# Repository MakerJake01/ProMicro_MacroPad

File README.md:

# ProMicro_MacroPad

**Overview** <br>
This project is for anyone who wants to make an 8 key MacroPad. The parts will most likely cost more than buying one. It can be used for keybinds in many programs. 
It's perfect for switching between scenes in OBS or a mute/unmute button in Discord. Some of the code is probably not the most efficient as I am a beginner. I am looking into making it work with QMK. 

<blockquote class="imgur-embed-pub" lang="en" data-id="a/6hcVxPT"  ><a href="//imgur.com/a/6hcVxPT">MacroPad pics</a></blockquote>

**The programing:** <br>
The code was all programmed in C++ using the Arduino IDE. It can be programmed with F keys (i.e. F13, F14, ...).
It uses the [keyboard.h](https://www.arduino.cc/reference/en/language/functions/usb/keyboard/) library. I have tried to make it as easy to reprogram as possible. 
It may be possible to program the MacroPad more efficiently. 

**The soldering:** <br>
There is a lot of SMD soldering. The smallest parts are 1206 resistors and capacitors. Some of the pads for the LEDs on the back do get very close. It will be an intermediate to advanced soldering project. (I have been soldering for a while so, SMD soldering is easy for me.) [SMD Soldering Guide](https://www.youtube.com/watch?v=VxMV6wGS3NY&t=544s)

**The PCB:** <br>
Use the Gerber files to make the PCBs. It's a two-layer PCB and a 1.6 mm board. A black solder mask will look better but will add some time and possible cost.  

**The switches** <br>
The PCB has the holes for an MX style switch. The PCB has the holes for a plate mount switch. If you have a PCB mount switch, the extra legs need to be cut off.

**Build guide** <br>
I am working on a multi-part build guide for my youtube channel.  
https://www.youtube.com/makerjake

**printed parts** <br>
I am having some trouble finding the STL files and my fusion 360 subscriptions has run out. I will try to either redesign the parts of finding the files. 

Creative Commons Attribution-NonCommercial 4.0 International License. cc-by-nc

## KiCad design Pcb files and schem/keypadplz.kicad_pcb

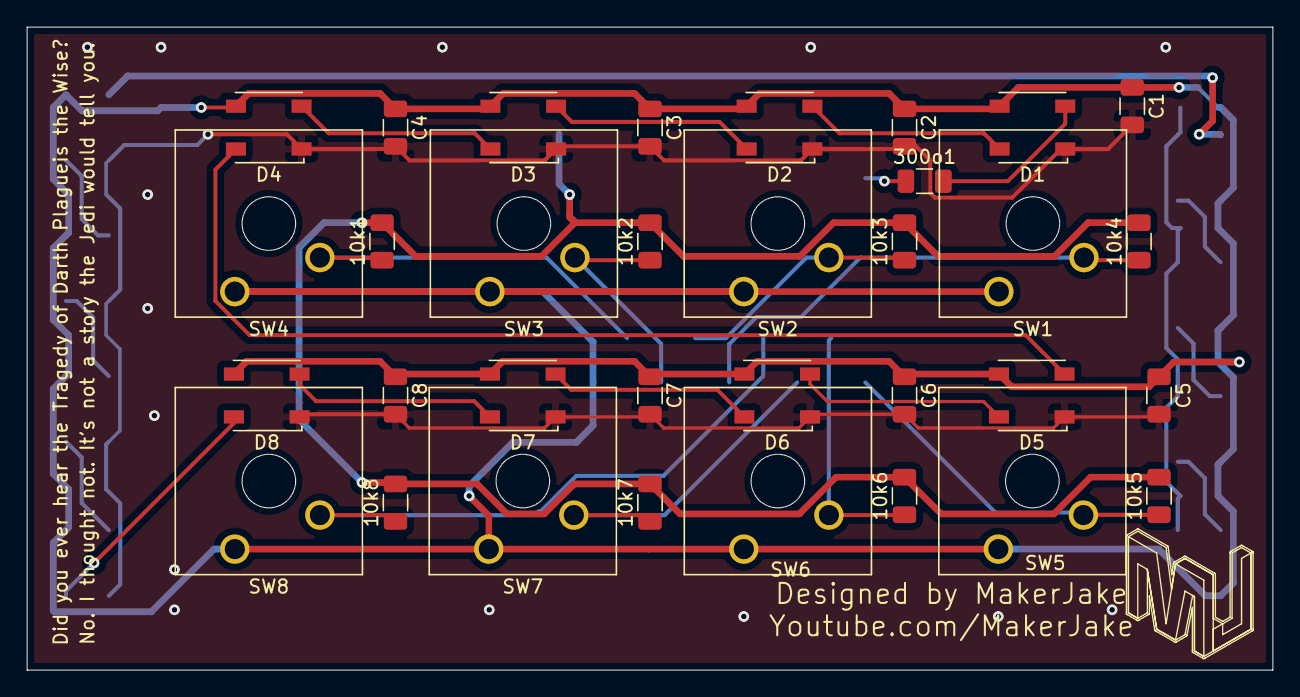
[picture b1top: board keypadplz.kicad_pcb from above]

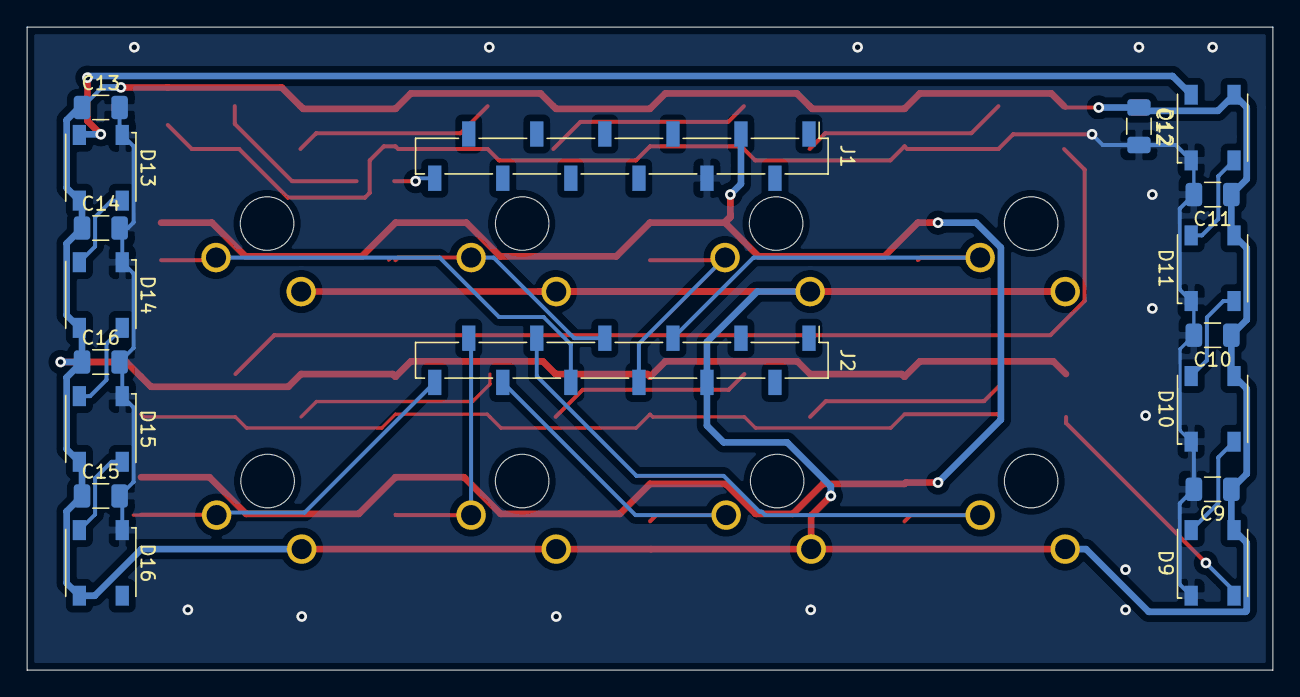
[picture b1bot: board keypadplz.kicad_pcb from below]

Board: 2 copper layers, 93.0 x 48.0 mm, 51 parts (18 on the bottom side), 28 nets.

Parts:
10k1, 10k2, 10k3, 10k4, 10k5, 10k6, 10k7, 10k8: R1; R_1206_3216Metric
300o1: R; R_1206_3216Metric
C1, C2, C3, C4, C5, C6, C7, C8, C9, C10, C11, C12, C13, C14, C15, C16: C_Small; C_1206_3216Metric
D1, D2, D3, D4, D5, D6, D7, D8, D9, D10, D11, D12, D13, D14, D15, D16: Inolux_IN-PI554FCH; LED_Inolux_IN-PI554FCH_PLCC4_5.0x5.0mm_P3.2mm
J1, J2: Conn_01x12_Male; PinSocket_1x12_P2.54mm_Vertical_SMD_Pin1Left
SW1, SW2, SW3, SW4, SW5, SW6, SW7, SW8: SW_Push; SW_Cherry_MX_1.00u_Plate

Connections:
GND: C1.2, C2.2, C3.2, C4.2, C5.2, C6.2, C7.2, C8.2, C9.2, C10.2, C11.2, C12.2, C13.2, C14.2, C15.2, C16.2, D1.1, D2.1, D3.1, D4.1, D5.1, D6.1, D7.1, D8.1, D9.1, D10.1, D11.1, D12.1, D13.1, D14.1, D15.1, D16.1, J1.4
unnamed: 10k1.1, J2.5, SW4.2
unnamed: 10k1.2, 10k2.2, 10k3.2, 10k4.2, 10k5.2, 10k6.2, 10k7.2, 10k8.2, J1.3
unnamed: 10k2.1, J2.6, SW3.2
unnamed: 10k3.1, J2.7, SW2.2
unnamed: 10k4.1, J2.8, SW1.2
unnamed: 10k5.1, J2.12, SW5.2
unnamed: 10k6.1, J2.11, SW6.2
unnamed: 10k7.1, J2.10, SW7.2
unnamed: 10k8.1, J2.9, SW8.2
unnamed: 300o1.1, J1.12
unnamed: 300o1.2, D1.2
unnamed: C1.1, C2.1, C3.1, C4.1, C5.1, C6.1, C7.1, C8.1, C9.1, C10.1, C11.1, C12.1, C13.1, C14.1, C15.1, C16.1, D1.3, D2.3, D3.3, D4.3, D5.3, D6.3, D7.3, D8.3, D9.3, D10.3, D11.3, D12.3, D13.3, D14.3, D15.3, D16.3, J2.4, SW1.1, SW2.1, SW3.1, SW4.1, SW5.1, SW6.1, SW7.1, SW8.1
unnamed: D1.4, D2.2
unnamed: D2.4, D3.2
unnamed: D3.4, D4.2
unnamed: D4.4, D5.2
unnamed: D5.4, D6.2
unnamed: D6.4, D7.2
unnamed: D7.4, D8.2
unnamed: D8.4, D9.2
unnamed: D9.4, D10.2
unnamed: D10.4, D11.2
unnamed: D11.4, D12.2
unnamed: D12.4, D13.2
unnamed: D13.4, D14.2
unnamed: D14.4, D15.2
unnamed: D15.4, D16.2

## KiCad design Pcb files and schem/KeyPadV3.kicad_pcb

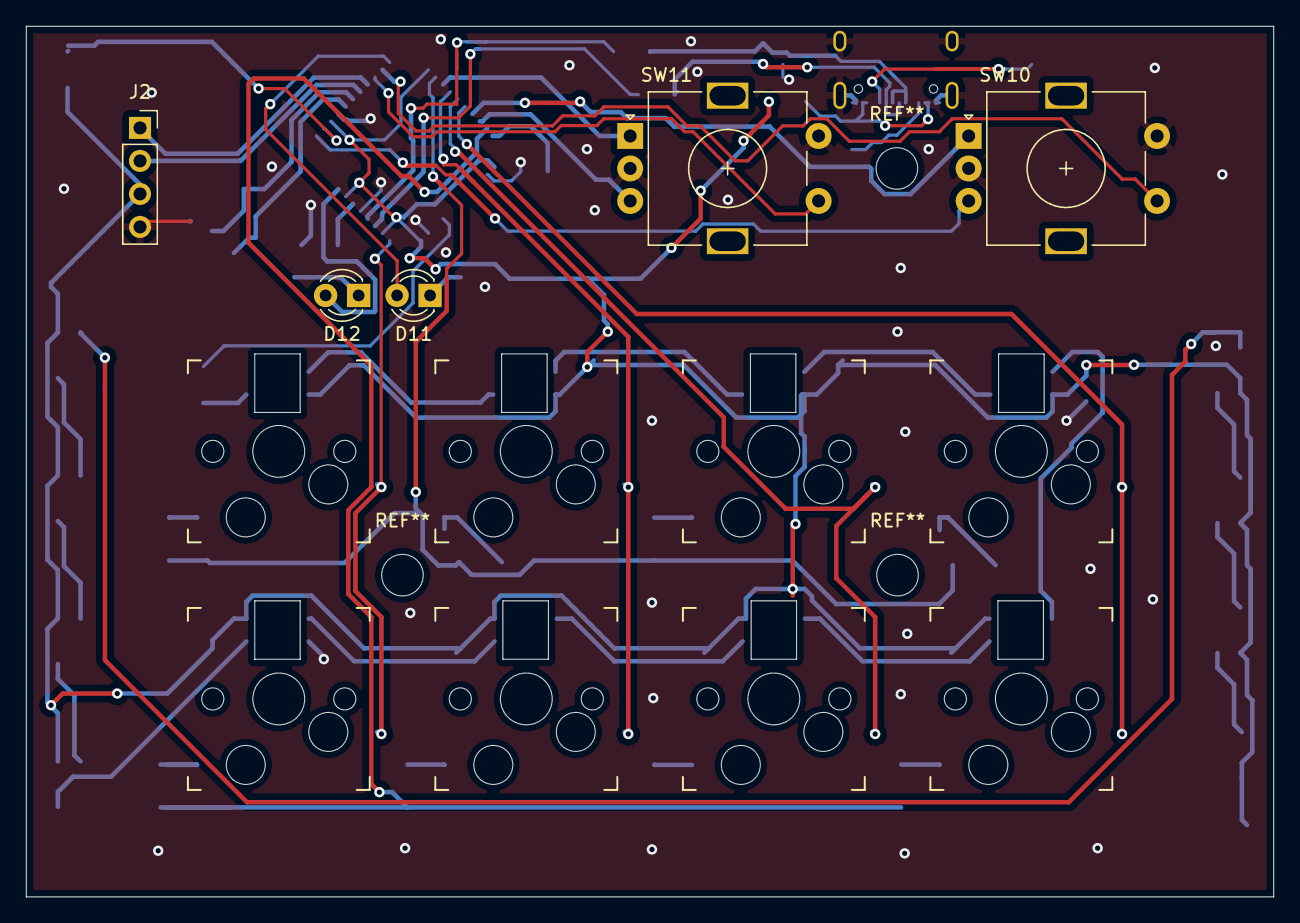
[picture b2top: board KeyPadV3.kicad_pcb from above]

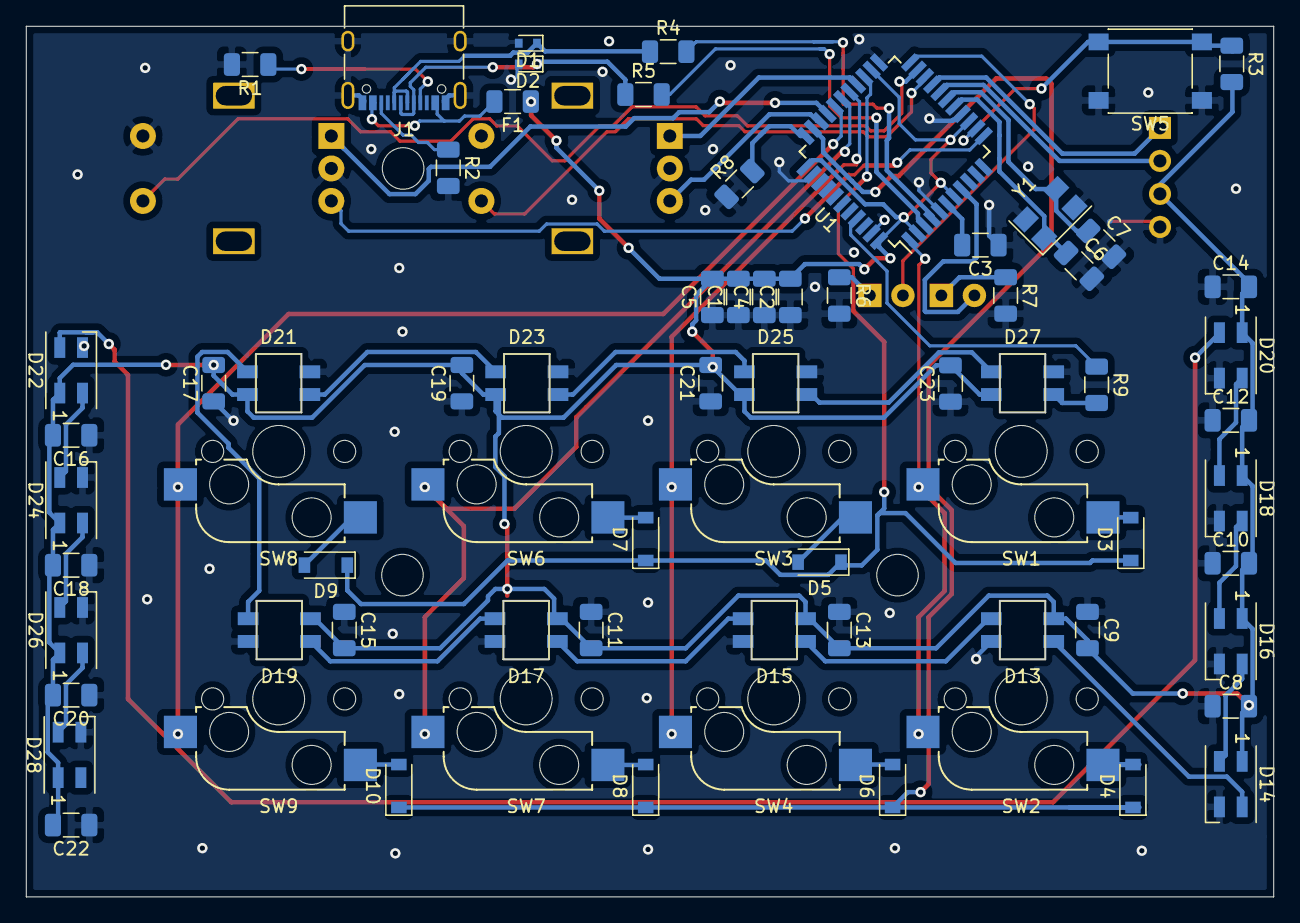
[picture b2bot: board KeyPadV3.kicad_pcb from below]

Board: 2 copper layers, 96.0 x 67.0 mm, 76 parts (63 on the bottom side), 57 nets.

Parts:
C1, C2, C4: 0.1uF; C_1206_3216Metric
C3: 1uF; C_1206_3216Metric
C5: 10uF; C_1206_3216Metric
C6, C7: 22pf; C_1206_3216Metric
C8, C9, C10, C11, C12, C13, C14, C15, C16, C17, C18, C19, C20, C21, C22, C23: .1uF; C_1206_3216Metric
D1, D2: DZ2S036X0L; D_SOD-523
D3, D4, D5, D6, D7, D8, D9, D10: D; D_SOD-123
D11, D12: LED; LED_D3.0mm
D13, D15, D17, D19, D21, D23, D25, D27: SK6812MINI; SK6812MINI_reverse
D14, D16, D18, D20, D22, D24, D26, D28: SK6812MINI; LED_SK6812MINI_PLCC4_3.5x3.5mm_P1.75mm
F1: Fuse; Fuse_1206_3216Metric
J1: USB_C_Receptacle_USB2.0; USB_C_Receptacle_XKB_U262-16XN-4BVC11
J2: Oled; PinSocket_1x04_P2.54mm_Vertical
R1, R2: 5.1k; R_1206_3216Metric
R3, R8: 10k; R_1206_3216Metric
R4, R5: 22; R_1206_3216Metric
R6, R7: 100; R_1206_3216Metric
R9: 500; R_1206_3216Metric
SW1, SW2, SW3, SW4, SW6, SW7, SW8, SW9: Switch_SW_Push; Kailh_socket_MX
SW5: SW_PUSH; SW_Push_1P1T_NO_6x6mm_H9.5mm
SW10, SW11: Rotary_Encoder_Switch; RotaryEncoder_Alps_EC11E-Switch_Vertical_H20mm
U1: ATMEGA32U4; TQFP-44_10x10mm_P0.8mm
Y1: Crystal_GND24_Small; Crystal_SMD_5032-4Pin_5.0x3.2mm

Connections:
+5V: C1.2, C2.2, C4.2, C5.2, C8.2, C9.2, C10.2, C11.2, C12.2, C13.2, C14.2, C15.2, C16.2, C17.2, C18.2, C19.2, C20.2, C21.2, C22.2, C23.2, D13.1, D14.1, D15.1, D16.1, D17.1, D18.1, D19.1, D20.1, D21.1, D22.1, D23.1, D24.1, D25.1, D26.1, D27.1, D28.1, F1.1, J2.3, R3.2, U1.2, U1.7, U1.14, U1.24, U1.34, U1.44
A1: SW10.A, U1.30
A2: SW11.A, U1.26
B1: SW10.B, U1.12
B2: SW11.B, U1.31
Col1: SW1.2, SW2.2, U1.1
Col2: SW3.2, SW4.2, U1.27
Col3: SW6.2, SW7.2, U1.28
Col4: SW8.2, SW9.2, U1.29
D+: D1.1, J1.A6, J1.B6, R4.1
D-: D2.1, J1.A7, J1.B7, R5.1
GND: C1.1, C2.1, C3.1, C4.1, C5.1, C6.2, C7.2, C8.1, C9.1, C10.1, C11.1, C12.1, C13.1, C14.1, C15.1, C16.1, C17.1, C18.1, C19.1, C20.1, C21.1, C22.1, C23.1, D1.2, D2.2, D13.3, D14.3, D15.3, D16.3, D17.3, D18.3, D19.3, D20.3, D21.3, D22.3, D23.3, D24.3, D25.3, D26.3, D27.3, D28.3, J1.A1, J1.A12, J1.B1, J1.B12, J1.S1, J2.4, R1.2, R2.2, R6.2, R7.2, R8.1, SW5.1, SW10.C, SW10.S2, SW11.C, SW11.S2, U1.5, U1.15, U1.23, U1.35, U1.43, Y1.2, Y1.4
Led: R9.1, U1.41
Led1: D11.2, U1.22
Led2: D12.2, U1.8
unnamed: C3.2, U1.6
unnamed: D3.2, SW1.1
unnamed: D4.2, SW2.1
unnamed: D5.2, SW3.1
unnamed: D6.2, SW4.1
unnamed: D7.2, SW6.1
unnamed: D8.2, SW7.1
unnamed: D9.2, SW8.1
unnamed: D10.2, SW9.1
unnamed: D11.1, R6.1
unnamed: D12.1, R7.1
unnamed: D13.2, D14.4
unnamed: D13.4, D15.2
unnamed: D14.2, D16.4
unnamed: D15.4, D17.2
unnamed: D16.2, D18.4
unnamed: D17.4, D19.2
unnamed: D18.2, D20.4
unnamed: D19.4, D21.2
unnamed: D20.2, D22.4
unnamed: D21.4, D23.2
unnamed: D22.2, D24.4
unnamed: D23.4, D25.2
unnamed: D24.2, D26.4
unnamed: D25.4, D27.2
unnamed: D26.2, D28.4
unnamed: D27.4, R9.2
unnamed: J1.A5, R1.1
unnamed: J1.B5, R2.1
unnamed: R3.1, SW5.2, U1.13
unnamed: R4.2, U1.4
unnamed: R5.2, U1.3
unnamed: R8.2, U1.33
Row1: D3.1, D5.1, D7.1, D9.1, U1.25
Row2: D4.1, D6.1, D8.1, D10.1, U1.32
S1: SW10.S1, U1.21
S2: SW11.S1, U1.20
SCL: J2.2, U1.18
SDA: J2.1, U1.19
VCC: F1.2, J1.A4, J1.A9, J1.B4, J1.B9
Xtal1: C6.1, U1.16, Y1.1
Xtal2: C7.1, U1.17, Y1.3

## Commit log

2020-08-17 Add files via upload
    This is a easy to edit version of the working Macropad code.
2020-08-17 Add files via upload
    These files are used in the production of the PCB.
2020-08-25 Update README.md
    Added more info.
2020-08-25 Create Parts_list
    Added parts list
2020-12-05 Update README.md
    added images
2020-12-05 Update README.md
    hope the images work now
2020-12-05 Update README.md
    Got some images
2021-01-04 Update MacroPad_Code.ino
    added some more code
2021-01-04 added the KiCad files and pcb files
2021-01-04 Update Parts_list
